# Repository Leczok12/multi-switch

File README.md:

# Multi-Switch

## Overview

The Multi-Switch project is built on the ESPHome system and features a setup with four buttons. Each button triggers different events: `pressed_short`, `pressed_long`, `pressed_double`, and `idle` (when there is no interaction with the buttons). This project is compatible with the Shelly Wall Switch 4.

## GPIO Pin Configuration

- **GPIO32** - sw_1
- **GPIO33** - sw_2
- **GPIO25** - sw_3
- **GPIO26** - sw_4
- **GPIO27** - software_res (unused)

## Events

- **pressed_short**: Triggered by a short press of a button.
- **pressed_long**: Triggered by a long press of a button.
- **pressed_double**: Triggered by a double press of a button.
- **idle**: Triggered when there is no interaction with the buttons.

## Images

### Top View

### Bottom View

## Parts List

| Part                          | Quantity |
| ----------------------------- | -------- |
| ESP32 Chip                    | 1x       |
| SMD Touch Buttons 3\*4\*2.5mm | 3x       |
| 2EDG 3.81mm 5-pin Connector   | 1x       |
| 2EDG 3.81mm 2-pin Connector   | 1x       |
| Hi-Link HLK-PM03 Power Supply | 1x       |
| SMD 0603 Green Diode          | 1x       |
| SMD 0805 Resistor 10k ohm     | 1x       |
| SMD 0805 Resistor 10 ohm      | 1x       |
| PCB Board                     | 1x       |

## License

This project is licensed under the MIT License - see the [LICENSE](LICENSE) file for details.

## Acknowledgments

Special thanks to the contributors and the ESPHome community for their continuous support and development of the platform.

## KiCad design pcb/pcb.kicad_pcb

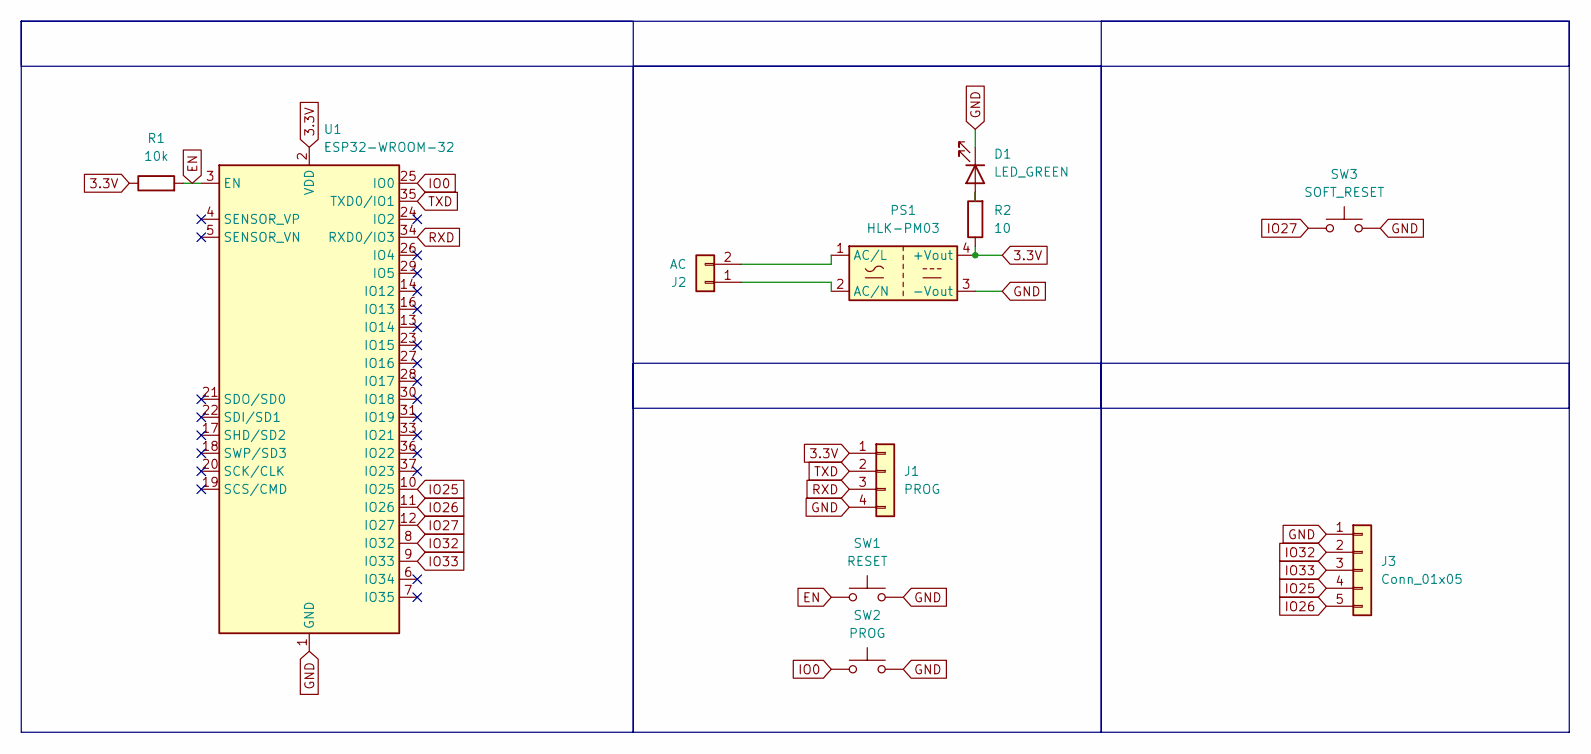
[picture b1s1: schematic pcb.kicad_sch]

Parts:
D1: LED_GREEN; LED_0603_1608Metric_Pad1.05x0.95mm_HandSolder
J1: PROG; PinHeader_1x04_P1.00mm_Vertical_SMD_Pin1Left
J2: AC; PhoenixContact_MCV_1,5_2-G-3.81_1x02_P3.81mm_Vertical
J3: Conn_01x05; PhoenixContact_MCV_1,5_5-G-3.81_1x05_P3.81mm_Vertical
PS1: HLK-PM03; Converter_ACDC_Hi-Link_HLK-PMxx
R1: 10k; R_0805_2012Metric_Pad1.20x1.40mm_HandSolder
R2: 10; R_0805_2012Metric_Pad1.20x1.40mm_HandSolder
SW1: RESET; SW_SPST_EVQP2
SW2: PROG; SW_SPST_EVQP2
SW3: SOFT_RESET; SW_SPST_EVQP2
U1: ESP32-WROOM-32

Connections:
3.3V: J1.1, PS1.4 (+Vout), R1.1, R2.1, U1.2 (VDD)
EN: R1.2, SW1.1, U1.3 (EN)
GND: D1.1 (K), J1.4, J3.1, PS1.3 (-Vout), SW1.2, SW2.2, SW3.2, U1.1 (GND), U1.15 (GND), U1.38 (GND), U1.39 (GND)
IO0: SW2.1, U1.25 (IO0)
IO25: J3.4, U1.10 (IO25)
IO26: J3.5, U1.11 (IO26)
IO27: SW3.1, U1.12 (IO27)
IO32: J3.2, U1.8 (IO32)
IO33: J3.3, U1.9 (IO33)
unnamed: D1.2 (A), R2.2
unnamed: J2.1, PS1.2 (AC/N)
unnamed: J2.2, PS1.1 (AC/L)
RXD: J1.3, U1.34 (RXD0/IO3)
TXD: J1.2, U1.35 (TXD0/IO1)

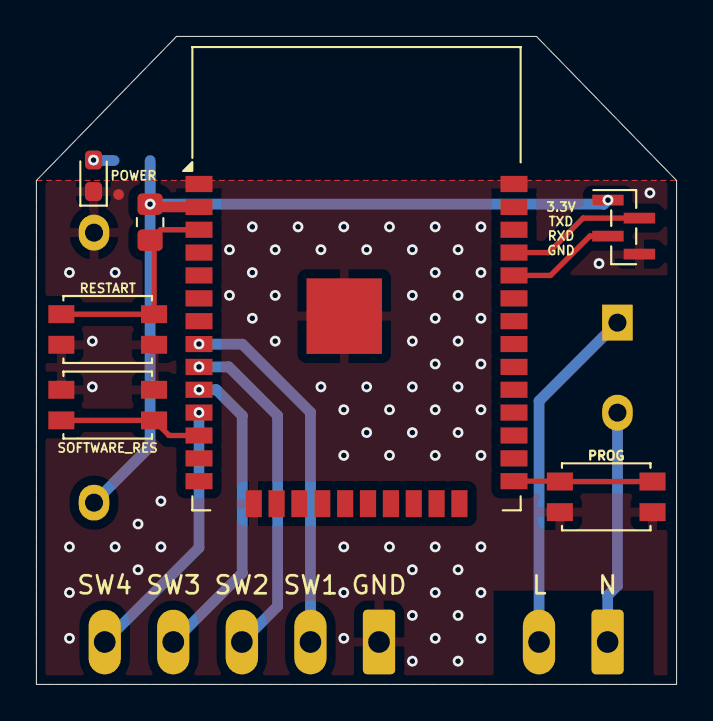
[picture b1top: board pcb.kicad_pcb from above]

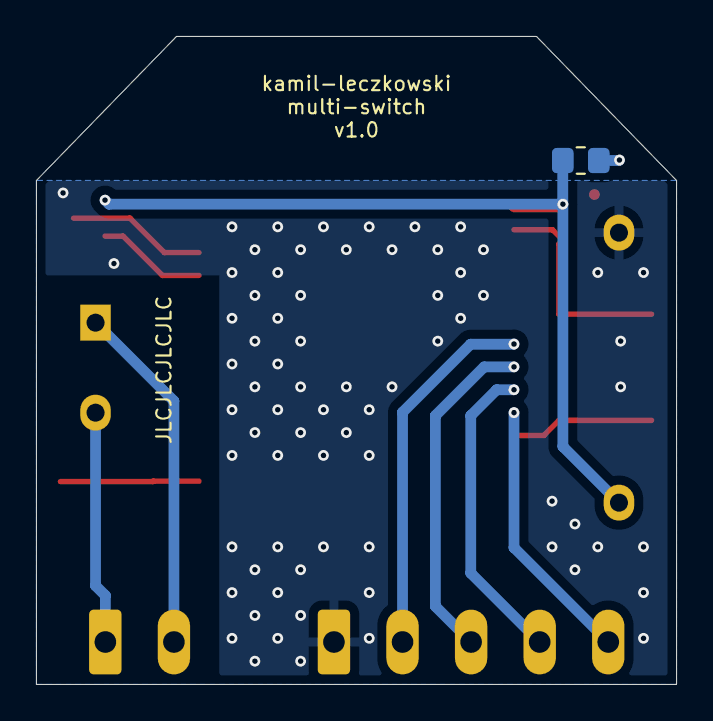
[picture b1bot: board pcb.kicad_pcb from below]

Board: 2 copper layers, 35.6 x 36.0 mm, 11 parts (4 on the bottom side), 14 nets.

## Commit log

2024-07-10 Create LICENSE
2024-07-10 readme
